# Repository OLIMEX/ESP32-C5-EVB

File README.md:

# ESP32-C5-EVB

Development board for dual band 2.4G and 5Ghz WiFi 6, Bluetooth 5 LE, Zigbee, Thread, Matter development board with Relays, optoisolated inputs and LiPo battery UPS

https://www.olimex.com/Products/IoT/ESP32-C5/ESP32-C5-EVB/open-source-hardware

## Licensee
* Hardware is released under CERN Open Hardware Licence Version 2 - Strongly Reciprocal
* SOFTWARE is released under MIT Licensee
* Documentation is released under CC BY-SA 4.0

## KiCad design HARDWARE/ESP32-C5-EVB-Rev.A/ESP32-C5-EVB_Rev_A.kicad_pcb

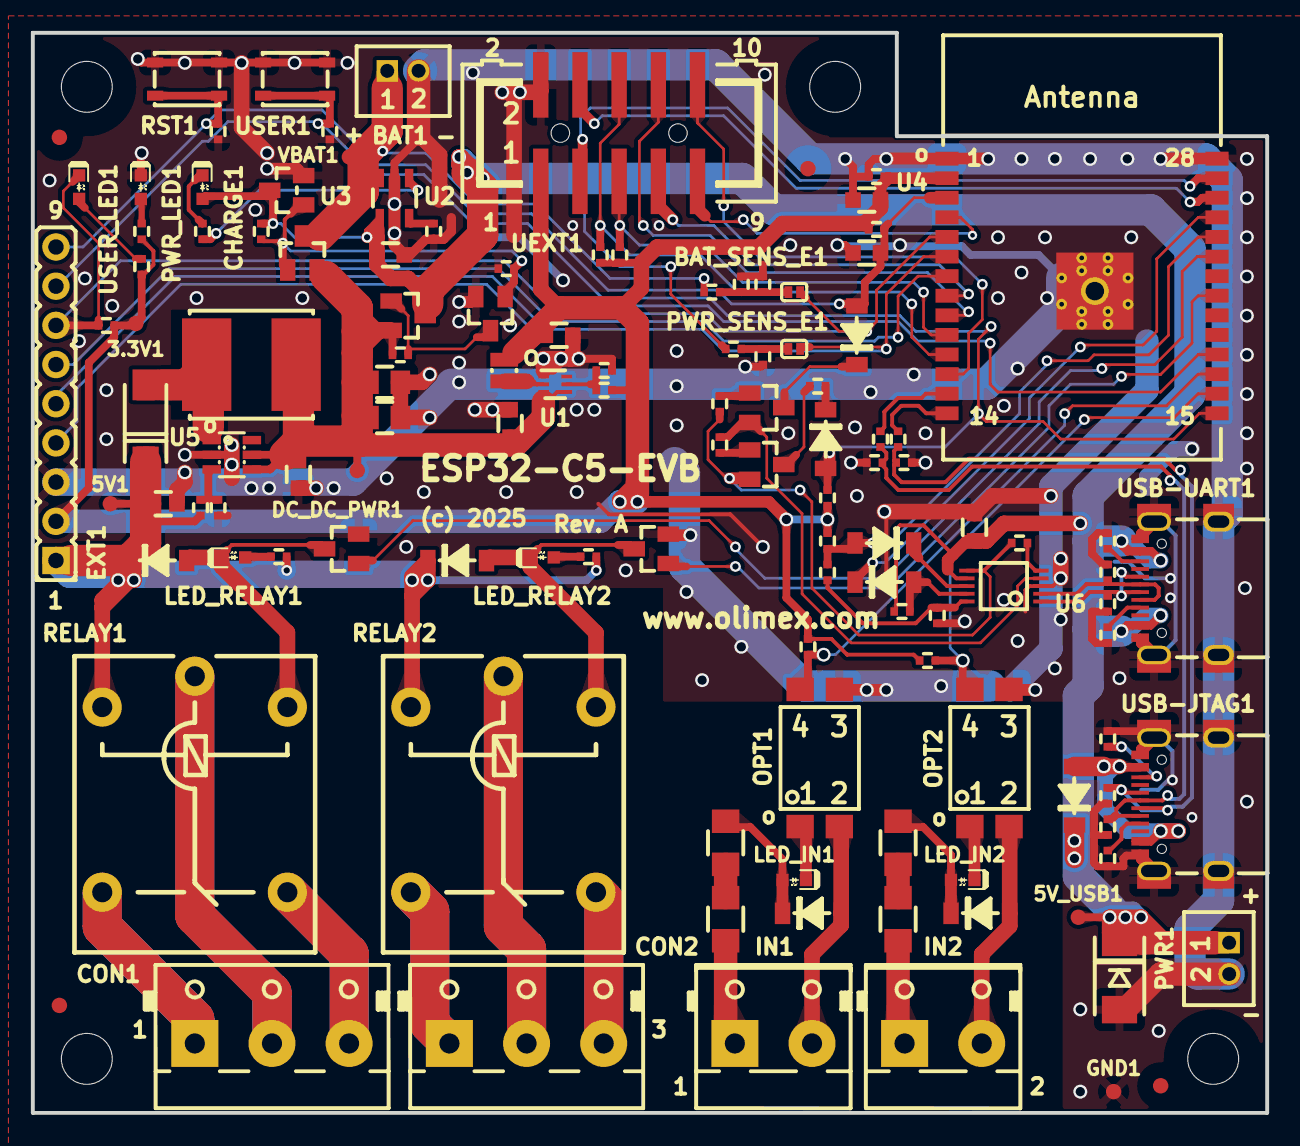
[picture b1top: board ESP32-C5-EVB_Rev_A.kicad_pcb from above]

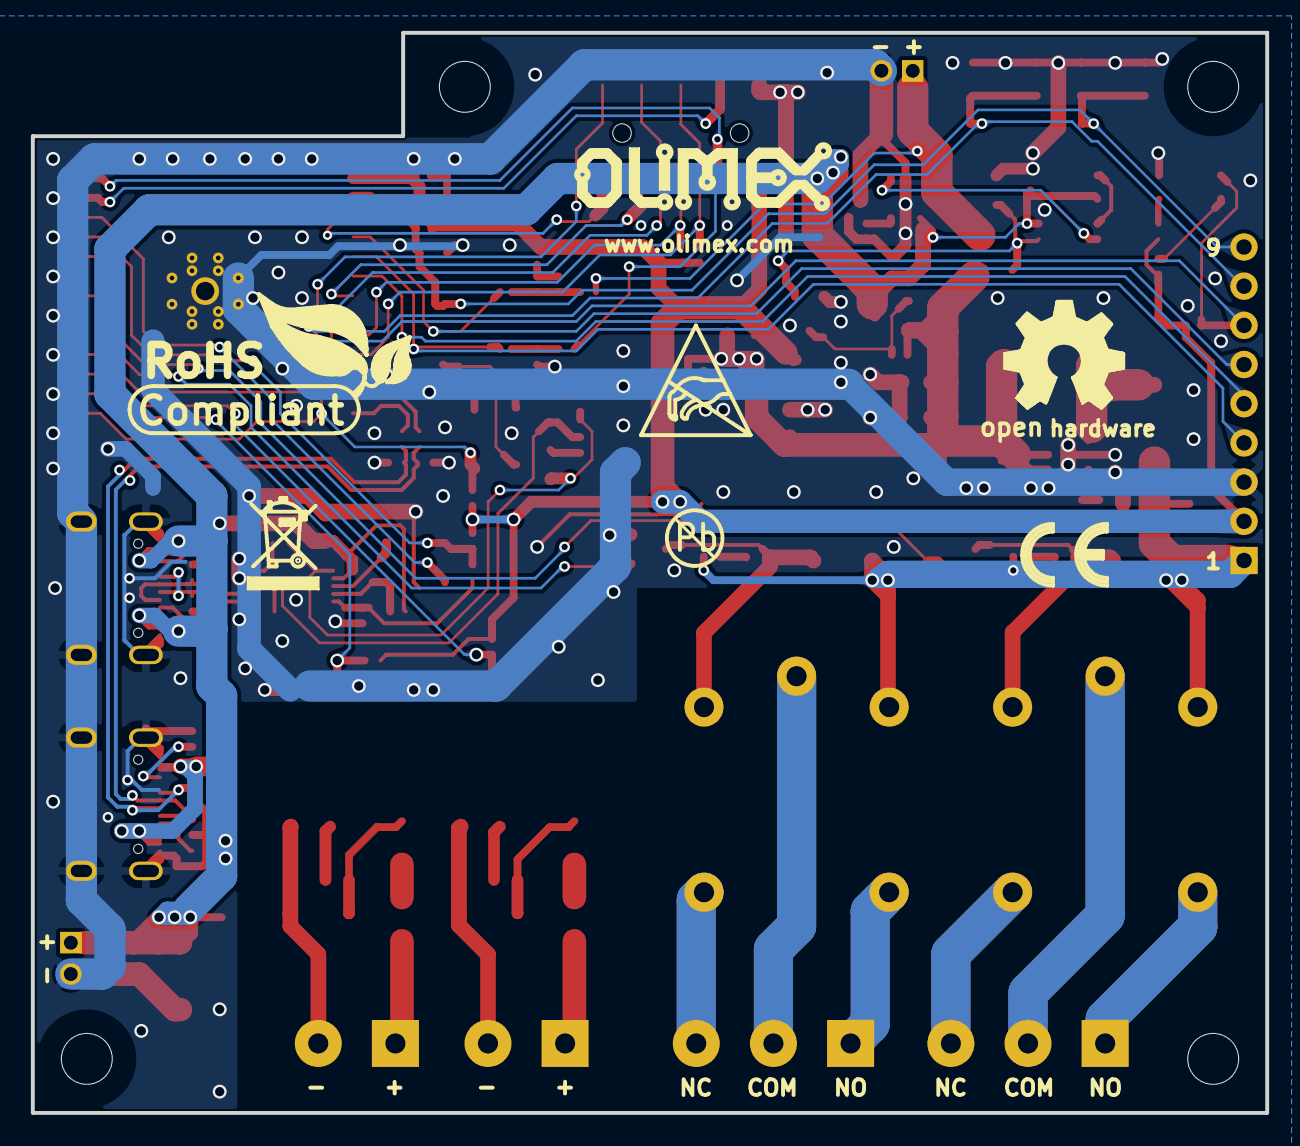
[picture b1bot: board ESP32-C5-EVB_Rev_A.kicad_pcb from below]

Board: 2 copper layers, 80.0 x 70.0 mm, 134 parts (7 on the bottom side), 81 nets.

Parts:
3.3V1, 5V1, 5V_USB1: TESTPAD; TESTPAD_40-ROUND
BAT1: DW02S; LIPO_BAT_VERTICAL_DW02S
BAT_SENS_E1: Opened; SJ_1_SMALLER
C1, C3, C4, C6, C10, C11, C13: 22uF/6.3V/20%/X5R/C0603; C_0603_5MIL_DWS
C2, C14: 100nF/10V/20%/X5R/C0402; C_0402_5MIL_DWS
C5: 1uF/10V/10%/X5R/C0603; C_0603_5MIL_DWS
C7, C8: NA(150pF/50V/2%/NP0/C0402); C_0402_5MIL_DWS
C9, C17: NA(47uF/6.3V/20%/X5R/C0805); C_0805_5MIL_DWS
C12: 1nF/X7R/50VDC; C_0402_5MIL_DWS
C15, C16: NA(100nF/10V/20%/X5R/C0402); C_0402_5MIL_DWS
CHARGE1: LED/Yellow/0603; LED_0603_KA
CON1, CON2: DG306-5.0-3P; TB3-DG306-5.0_3P
D1: 1N5822/SS34/SMA; SMA-KA
D2: SMBJ6.0A; DO214AA_1(K)-2(A)
D3, D4, D5, D6, D7: 1N5819S4(SOD-123); SOD-123_1C-2A_KA
D8, D9, D10, D11: 1N4148W(SOD-123); SOD-123_1C-2A_KA
DC_DC_PWR1: TESTPAD; TESTPAD_40-ROUND
EXT1: NA; HN1x9
FET1, FET3: IRLML6402(SOT-23); SOT23
FET2: BSS138(SOT-23); SOT23
FID1, FID2: Fiducial; Fiducial1x3
FID3, FID4: Fiducial; Fiducial1x3_Paste
GND1: TESTPAD; TESTPAD_40-ROUND
IN1, IN2: DG306-5.0-2P; TB2-DG306-5.0_2P
L1: 1.0uH/4.2A/DCR=35mR/20%/2.00x1.60x1.00mm/L2016(PI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; L_2016_MM
L2: 2.2uH/3A/YS75/7x8; YS75_7X8MM
LED_IN1, LED_IN2: LED/Red/0603; LED_0603_KA
LED_RELAY1, LED_RELAY2: LED/Green/0603; LED_0603_KA
Logo_OLIMEX_TB: Logo_OLIMEX_TB
MH1, MH2, MH3, MH4: Mounting_Hole_NPTH; Mounting_hole_3.3mm
OPT1, OPT2: PC817CS_CYPC817(C-TP2); H11A817C_SMD(PC817X3NIP06)_FP
PWR1: DW02S; LIPO_BAT_VERTICAL_DW02S
PWR_LED1: LED/Red/0603; LED_0603_KA
PWR_SENS_E1: Opened; SJ_1_SMALLER
Q1, Q2: BC817-40(SOT23); SOT23
R1, R26, R27, R30, R31, R32, R35: 2.2k/R0402; R_0402_5MIL_DWS
R2: 180k/1%/R0402; R_0402_5MIL_DWS
R3, R4, R5, R17, R18, R28, R29: 10k/R0402; R_0402_5MIL_DWS
R6: 10k/1%/R0402; R_0402_5MIL_DWS
R7, R15: 40.2k/1%/R0402; R_0402_5MIL_DWS
R8: 1M/R0402; R_0402_5MIL_DWS
R9, R10: 33R/R0402; R_0402_5MIL_DWS
R11: 8.25k/1%/R0402; R_0402_5MIL_DWS
R12: 27k/1%/R0402; R_0402_5MIL_DWS
R13: 470k/R0402; R_0402_5MIL_DWS
R14: 1.1k/1%/R0402; R_0402_5MIL_DWS
R16: 220k/R0402; R_0402_5MIL_DWS
R19: NA(10k/R0402); R_0402_5MIL_DWS
R20, R24: 1k/R0402; R_0402_5MIL_DWS
R21: 4.7k/R0402; R_0402_5MIL_DWS
R22, R23, R33, R34: 5.1k/1%/R0402; R_0402_5MIL_DWS
R25: 220R/R0402; R_0402_5MIL_DWS
R36, R38, R40, R41: 150k/R1206; R_1206_5MIL_DWS
R37, R39: 47k/R0402; R_0402_5MIL_DWS
RELAY1, RELAY2: RAS-0515; Relay_RAS-05-15_DrillSlot
RST1: YTS-A016-X
Sign_Antistatic: Sign_Antistatic
Sign_CE: CE_Sign
Sign_OSHW_8x8: Sign_OSHW_8x8
Sign_PB-Free: Sign_PB-Free
Sign_RecycleBin_1: Sign_RecycleBin_1
Sign_RoHS_1: Sign_RoHS_1
T1, T2: LMUN2235LT1G(SOT-23); SOT23
TVS1, TVS2, TVS3, TVS4: GG0402052R542P; D_0402_5MIL_DWS
U1: TPS62A02ADRLR(SOT-563-6); SOT-563-6
U2: TP4054-42-SOT25-R; SOT-23-5
U3: VDA4710CTA; SOT-23
U4: ESP32-C5-WROOM-1-N8R4; ESP32-C5-WROOM-1-N**4-UNIVERSAL_MODULE
U5: MT3608(SOT23-6); SOT23-6
U6: CH340X(MSOP-10); MSOP-10_Pitch-0.5mm_3.00x3.00x1.00mm
UEXT1: P-B-V-10-LF; GBH-254-SMT-10
USB-JTAG1: USB-C-16P-F(A40-00119-A52-12); USB2.0_TYPE-C(A40-00119-A52-12)_Paste
USB-UART1: USB-C-16P-F(A40-00119-A52-12); USB2.0_TYPE-C(A40-00119-A52-12)_Paste
USER1: YTS-A016-X
USER_LED1: LED/Green/0603; LED_0603_KA
VBAT1: TESTPAD; TESTPAD_40-ROUND

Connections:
+3.3V: 3.3V1.1 (Pad), C1.1, C2.2, C4.1, EXT1.2, L1.2, R2.2, R3.1, R19.2, R26.1, R27.2, R28.2, R29.2, R31.1, R32.1, R37.2, R39.2, U4.2 (3V3), UEXT1.1
+5V: 5V1.1 (Pad), C11.2, D1.1 (K), D8.1 (K), D9.1 (K), EXT1.1, R11.1, R30.2, R35.2, RELAY1.1, RELAY2.1
+5V_USB: 5V_USB1.1 (Pad), C6.1, C13.1, CHARGE1.2 (A), D2.1 (K), D7.1 (K), FET3.3, PWR1.1, R5.2, R12.1, R17.1, U2.4 (VCC), U3.3 (VIn), U6.7 (VCC), USB-UART1.A4 (VBUS), USB-UART1.A9 (VBUS), USB-UART1.B4 (VBUS), USB-UART1.B9 (VBUS)
/D+: TVS1.1 (IO1), U6.1 (UD+), USB-UART1.A6 (DP1), USB-UART1.B6 (DP2)
/D-: TVS2.1 (IO1), U6.2 (UD-), USB-UART1.A7 (DN1), USB-UART1.B7 (DN2)
/ESP_EN: C5.1, C15.1, D5.2 (A), EXT1.9, R3.2, RST1.1, U4.3 (EN)
/GPIO0/EXT_PWR_SEN: EXT1.4, PWR_SENS_E1.2, U4.6 (IO0/GPIO0/XTAL_32K_P/LP_GPIO0/LP_UART_D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)
/GPIO1: EXT1.5, U4.7 (IO1/GPIO1/XTAL_32K_N/LP_GPIO1/LP_UART_D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)
/GPIO2/SPI2_CLK: U4.4 (IO2/MTMS/GPIO2/LP_GPIO2/LP_UART_RTSN/LP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), UEXT1.9
/GPIO3/BAT_SEN: BAT_SENS_E1.2, EXT1.6, U4.5 (IO3/MTDI/GPIO3/LP_GPIO3/LP_UART_CTSN/LP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)
/GPIO4/IN2: OPT1.4 (C), R37.1, U4.17 (IO4/MTCK/GPIO4/LP_GPIO4/LP_UART_RXD/ADC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)
/GPIO5/IN1: OPT2.4 (C), R39.1, U4.16 (IO5/MTDO/GPIO5/LP_GPIO5/LP_UART_TXD/ADC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)
/GPIO6/SPI2_MISO: U4.8 (IO6/GPIO6/LP_GPIO6/ADC1_CH5/FSPICLK), UEXT1.7
/GPIO7/SPI2_MOSI: U4.9 (IO7/GPIO7/LP_GPIO7/FSPID/SDIO_DATA1), UEXT1.8
/GPIO8/I2C_SCK: R26.2, U4.10 (IO8/GPIO8/PAD_COMP0/SDIO_DATA0), UEXT1.5
/GPIO9/I2C_SDA: R27.1, U4.11 (IO9/GPIO9/PAD_COMP1/SDIO_CLK), UEXT1.6
/GPIO10/SPI2_CS: U4.12 (IO10/GPIO10/FSPICS0/SDIO_CMD), UEXT1.10
/GPIO11/U0TXD: D4.1 (K), U4.25 (IO11/U0TXD/GPIO11)
/GPIO12/U0RXD: D3.2 (A), R18.2, R19.1, U4.24 (IO12/U0RXD/GPIO12)
/GPIO23/REL2: T2.1 (B), U4.21 (IO23/GPIO23)
/GPIO24/REL1: T1.1 (B), U4.23 (IO24/GPIO24)
/GPIO25/U1RXD: U4.26 (IO25/GPIO25), UEXT1.4
/GPIO26/U1TXD: U4.27 (IO26/GPIO26), UEXT1.3
/GPIO27/USER_LED: EXT1.7, R29.1, U4.18 (IO27/GPIO27), USER_LED1.1 (K)
/GPIO28/USER_BUT: C16.1, D6.2 (A), EXT1.8, R28.1, U4.15 (IO28/GPIO28), USER1.1
/USB_CC1: R34.2, USB-JTAG1.A5 (CC1)
/USB_CC2: R33.2, USB-JTAG1.B5 (CC2)
/USB_D+: C7.1, R10.2, TVS3.1 (IO1), USB-JTAG1.A6 (DP1), USB-JTAG1.B6 (DP2)
/USB_D-: C8.1, R9.1, TVS4.1 (IO1), USB-JTAG1.A7 (DN1), USB-JTAG1.B7 (DN2)
GND: BAT1.2, C1.2, C2.1, C3.2, C4.2, C5.2, C6.2, C7.2, C8.2, C9.2, C10.1, C11.1, C12.2, C13.2, C14.2, C15.2, C16.2, C17.2, D2.2 (A), EXT1.3, FET2.2 (S), GND1.1 (Pad), OPT1.3 (E), OPT2.3 (E), PWR1.2, PWR_LED1.1 (K), R6.1, R7.2, R8.2, R14.2, R15.2, R16.2, R22.1, R23.1, R33.1, R34.1, RST1.2, T1.2 (E), T2.2 (E), TVS1.2 (IO2), TVS2.2 (IO2), TVS3.2 (IO2), TVS4.2 (IO2), U1.1 (GND), U2.2 (GND), U3.2 (Vss), U4.1 (GND), U4.28 (GND), U4.29 (EPAD), U5.2 (GND), U6.3 (GND), UEXT1.2, USB-JTAG1.0 (SHELL), USB-JTAG1.A1 (GND), USB-JTAG1.A12 (GND), USB-JTAG1.B1 (GND), USB-JTAG1.B12 (GND), USB-UART1.0 (SHELL), USB-UART1.A1 (GND), USB-UART1.A12 (GND), USB-UART1.B1 (GND), USB-UART1.B12 (GND), USER1.2
unnamed: BAT_SENS_E1.1, C12.1, R13.2, R16.1
unnamed: CHARGE1.1 (K), R1.1
unnamed: CON1.1, RELAY1.NO0
unnamed: CON1.2, RELAY1.COM0
unnamed: CON1.3, RELAY1.NC0
unnamed: CON2.1, RELAY2.NO0
unnamed: CON2.2, RELAY2.COM0
unnamed: CON2.3, RELAY2.NC0
unnamed: D1.2 (A), L2.2, U5.1 (LX)
unnamed: D3.1 (K), U6.8 (TXD)
unnamed: D4.2 (A), R17.2, U6.9 (RXD)
unnamed: D5.1 (K), Q1.3 (C)
unnamed: D6.1 (K), R25.2
unnamed: D7.2 (A), USB-JTAG1.A4 (VBUS), USB-JTAG1.A9 (VBUS), USB-JTAG1.B4 (VBUS), USB-JTAG1.B9 (VBUS)
unnamed: D8.2 (A), LED_RELAY1.1 (K), RELAY1.2, T1.3 (C)
unnamed: D9.2 (A), LED_RELAY2.1 (K), RELAY2.2, T2.3 (C)
unnamed: D10.2 (A), IN1.2, OPT1.2 (K)
unnamed: D10.1 (K), LED_IN1.2 (A), R40.2
unnamed: D11.2 (A), IN2.2, OPT2.2 (K)
unnamed: D11.1 (K), LED_IN2.2 (A), R41.2
unnamed: FET2.3 (D), FET3.1, R4.1
unnamed: FET1.1, FET2.1 (G), R5.1, R8.1, U3.1 (VOut)
unnamed: IN1.1, R36.1
unnamed: IN2.1, R38.1
unnamed: LED_IN1.1 (K), OPT1.1 (A)
unnamed: LED_IN2.1 (K), OPT2.1 (A)
unnamed: LED_RELAY1.2 (A), R30.1
unnamed: LED_RELAY2.2 (A), R35.1
unnamed: PWR_LED1.2 (A), R32.2
unnamed: PWR_SENS_E1.1, R12.2, R15.1
unnamed: Q1.1 (B), R20.2
unnamed: Q1.2 (E), R24.1, U6.4 (RTS#)
unnamed: Q2.1 (B), R24.2
unnamed: Q2.3 (C), R25.1
unnamed: Q2.2 (E), R20.1, R21.1, U6.6 (TNOW/DTR#)
unnamed: R36.2, R40.1
unnamed: R38.2, R41.1
unnamed: C3.1, C9.1, C10.2, C17.1, DC_DC_PWR1.1 (Pad), FET1.2, FET3.2, L2.1, R4.2, U1.3 (VIN), U1.4 (EN), U5.4 (EN), U5.5 (IN)
unnamed: R2.1, R7.1, U1.5 (FB)
unnamed: L1.1, U1.2 (SW)
unnamed: R1.2, U2.1 (CHRGb)
unnamed: R6.2, U2.5 (PROG)
unnamed: R9.2, U4.13 (IO13/GPIO13/USB_D-/SDIO_DATA3)
unnamed: R10.1, U4.14 (IO14/GPIO14/USB_D+/SDIO_DATA2)
unnamed: R11.2, R14.1, U5.3 (FB)
unnamed: R21.2, U6.5 (CTS#)
unnamed: C14.1, R18.1, U6.10 (V3)
unnamed: R23.2, USB-UART1.A5 (CC1)
unnamed: R22.2, USB-UART1.B5 (CC2)
unnamed: R31.2, USER_LED1.2 (A)
VBAT: BAT1.1, FET1.3, R13.1, U2.3 (VBAT), VBAT1.1 (Pad)

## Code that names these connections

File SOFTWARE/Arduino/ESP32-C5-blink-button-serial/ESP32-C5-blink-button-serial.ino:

/*
  Olimex ESP32-C5-EVB Demo
  Demonstrates user button + LED feedback via USB-UART1 (CH340)

  Pins (per schematic):
    USER_LED  -> GPIO27 (active LOW)
    USER_BTN  -> GPIO28 (active LOW, pulled up)
    UART0 TXD -> GPIO11 (to CH340 RX)
    UART0 RXD -> GPIO12 (from CH340 TX)

  Board Manager Settings:
    - PSRAM: Enabled
    - USB CDC on Boot: Disabled
    - The COM port associated with the board

  Behavior for test:
    - Press the User button -> LED turns ON
    - Release the User button -> LED turns OFF
    - Serial output shows button state in real-time
*/

#include "Arduino.h"

// Pin definitions
#define USER_LED 27
#define USER_BTN 28

void setup() {
  pinMode(USER_LED, OUTPUT);        // LED output (active LOW)
  pinMode(USER_BTN, INPUT_PULLUP);  // Button input (active LOW)

  // Initialize UART0 (USB-UART1 via CH340)
  Serial.begin(115200);
  while (!Serial) {} // wait for serial to be ready (optional)
  Serial.println("ESP32-C5-EVB Button & LED Demo started");
}

void loop() {
  // Read button state (active LOW)
  bool buttonPressed = digitalRead(USER_BTN) == LOW;

  // LED logic inverted because LED is active LOW
  digitalWrite(USER_LED, buttonPressed ? LOW : HIGH);

  // Print button state over USB-UART
  if (buttonPressed) {
    Serial.println("Button pressed -> LED ON");
  } else {
    Serial.println("Button released -> LED OFF");
  }

  delay(100); // debounce & readability
}

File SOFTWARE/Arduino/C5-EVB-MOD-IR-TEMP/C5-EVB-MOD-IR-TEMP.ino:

/*
  Olimex ESP32-C5-EVB + MOD-IR-TEMP (MLX90614) Demo
  ---------------------------------------------------------
  Demonstrates how to read infrared temperature data from the MLX90614
  connected via the UEXT port (I2C interface).

  Hardware connections (UEXT pinout):
    UEXT Pin 3 -> SDA  -> ESP32-C5 GPIO9
    UEXT Pin 4 -> SCL  -> ESP32-C5 GPIO8
    UEXT Pin 1 -> 3.3V (sensor power)
    UEXT Pin 2 -> GND  (ground)

  Requirements:
    - Arduino IDE with ESP32 board support installed
    - Adafruit MLX90614 library (install via Library Manager)
      → Tools > Manage Libraries > search "Adafruit MLX90614"
    - Board selected: "ESP32C5 Dev Module" 

  Functionality:
    - Initializes I2C communication on GPIO2/GPIO3
    - Reads ambient and object temperature every second
    - Prints results over USB serial
    
  Date: 2025-11-13
*/

#include <Wire.h>
#include <Adafruit_MLX90614.h>

// Create MLX90614 object
Adafruit_MLX90614 mlx = Adafruit_MLX90614();

// Define I2C pins for ESP32-C5-EVB (UEXT connector)
#define SDA_PIN 9
#define SCL_PIN 8

void setup() {
  // Start serial communication
  Serial.begin(115200);
  delay(1000);
  Serial.println("\n=== Olimex ESP32-C5-EVB + MOD-IR-TEMP (MLX90614) Demo ===");
  Serial.println("Initializing I2C and MLX90614 sensor...");

  // Initialize I2C on custom pins
  Wire.begin(SDA_PIN, SCL_PIN);

  // Initialize the MLX90614 sensor
  if (!mlx.begin()) {
    Serial.println("Error: MLX90614 not detected! Check wiring and power.");
    while (true) {
      delay(1000);
      Serial.println("Retrying...");
    }
  }

  Serial.println("MLX90614 detected successfully!");
  Serial.println("-----------------------------------------------------");
  Serial.println("Ambient and Object temperatures will be printed below:");
}

void loop() {
  // Read ambient temperature (air around the sensor)
  double ambientTemp = mlx.readAmbientTempC();

  // Read object temperature (measured by IR)
  double objectTemp = mlx.readObjectTempC();

  // Print to Serial Monitor
  Serial.print("Ambient: ");
  Serial.print(ambientTemp, 2);
  Serial.print(" °C   |   Object: ");
  Serial.print(objectTemp, 2);
  Serial.println(" °C");

  // Wait before next reading
  delay(1000);
}

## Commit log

2025-09-11 initial upload
2025-11-11 Update
    Added SOFTWARE demos for Arduino and ESP-IDF
2025-11-11 Update
    Relay demo for Arduino
2025-11-13 Update
    New demo with MOD-IR-TEMP

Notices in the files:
HARDWARE/ESP32-C5-EVB-Rev.A/ESP32-C5-EVB_Rev_A.kicad_pcb:
(c) 2025
